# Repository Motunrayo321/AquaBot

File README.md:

# Rotatory-Distribution-System

combined_tests: tests the combined action of the different components. The fullTest() function tests the entire operation of the system.

unit_tests: used to test the operation of individual components

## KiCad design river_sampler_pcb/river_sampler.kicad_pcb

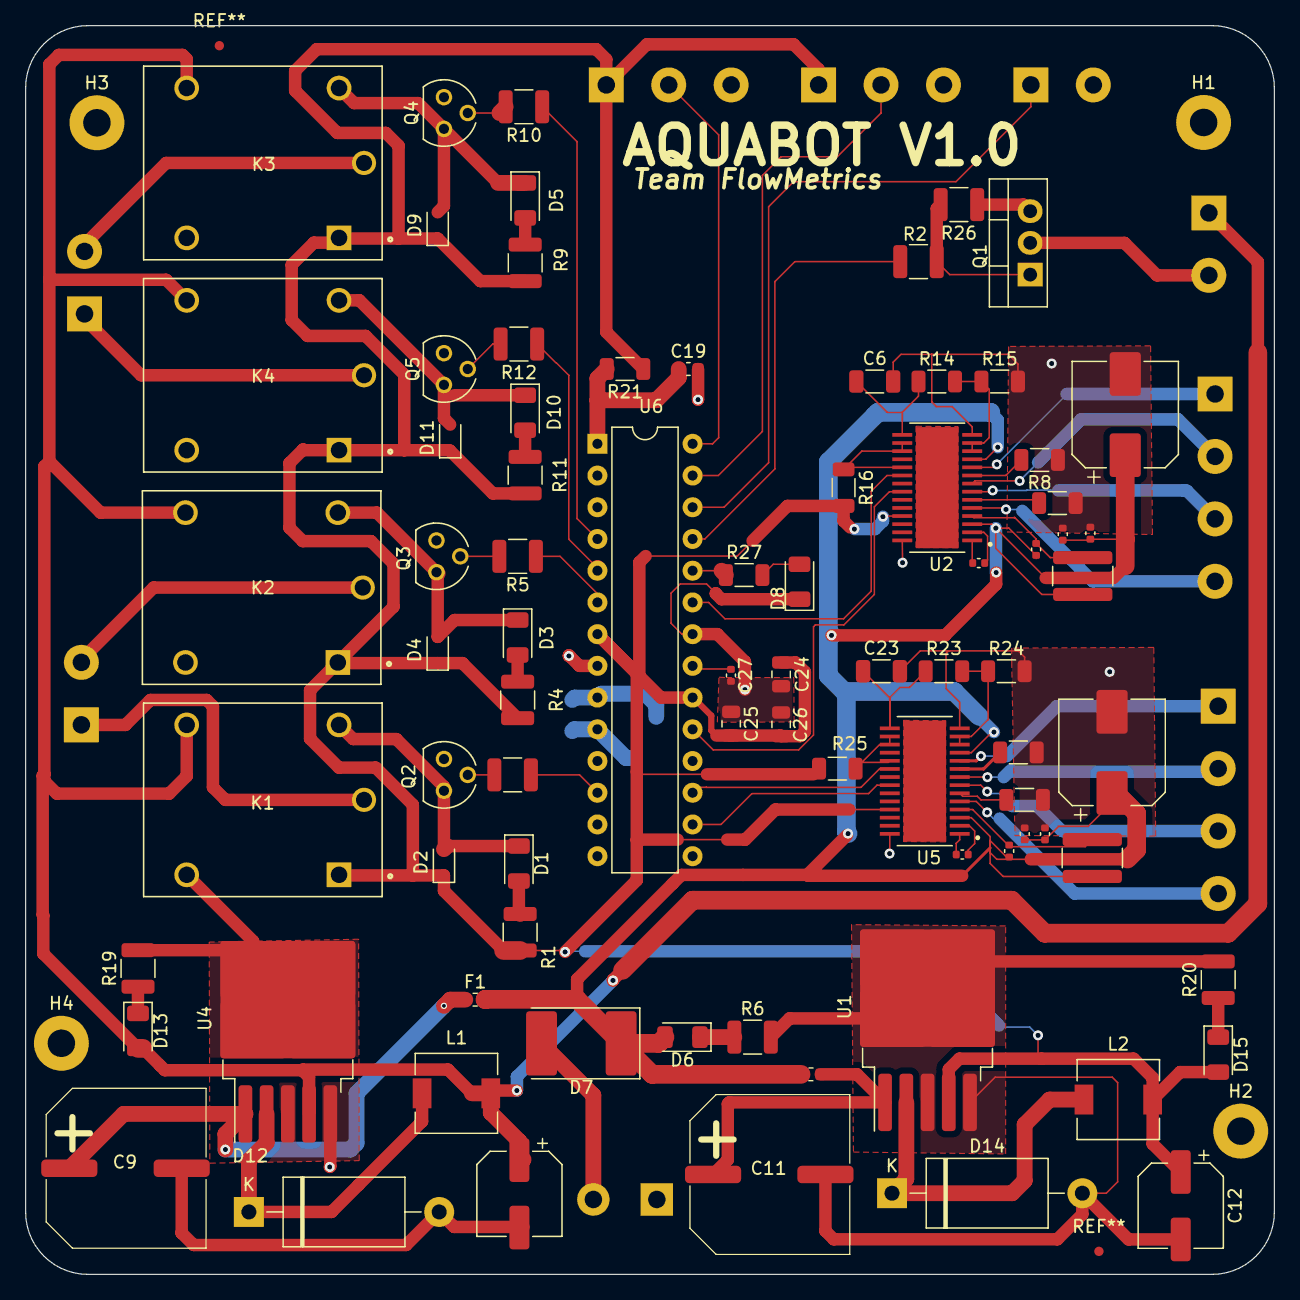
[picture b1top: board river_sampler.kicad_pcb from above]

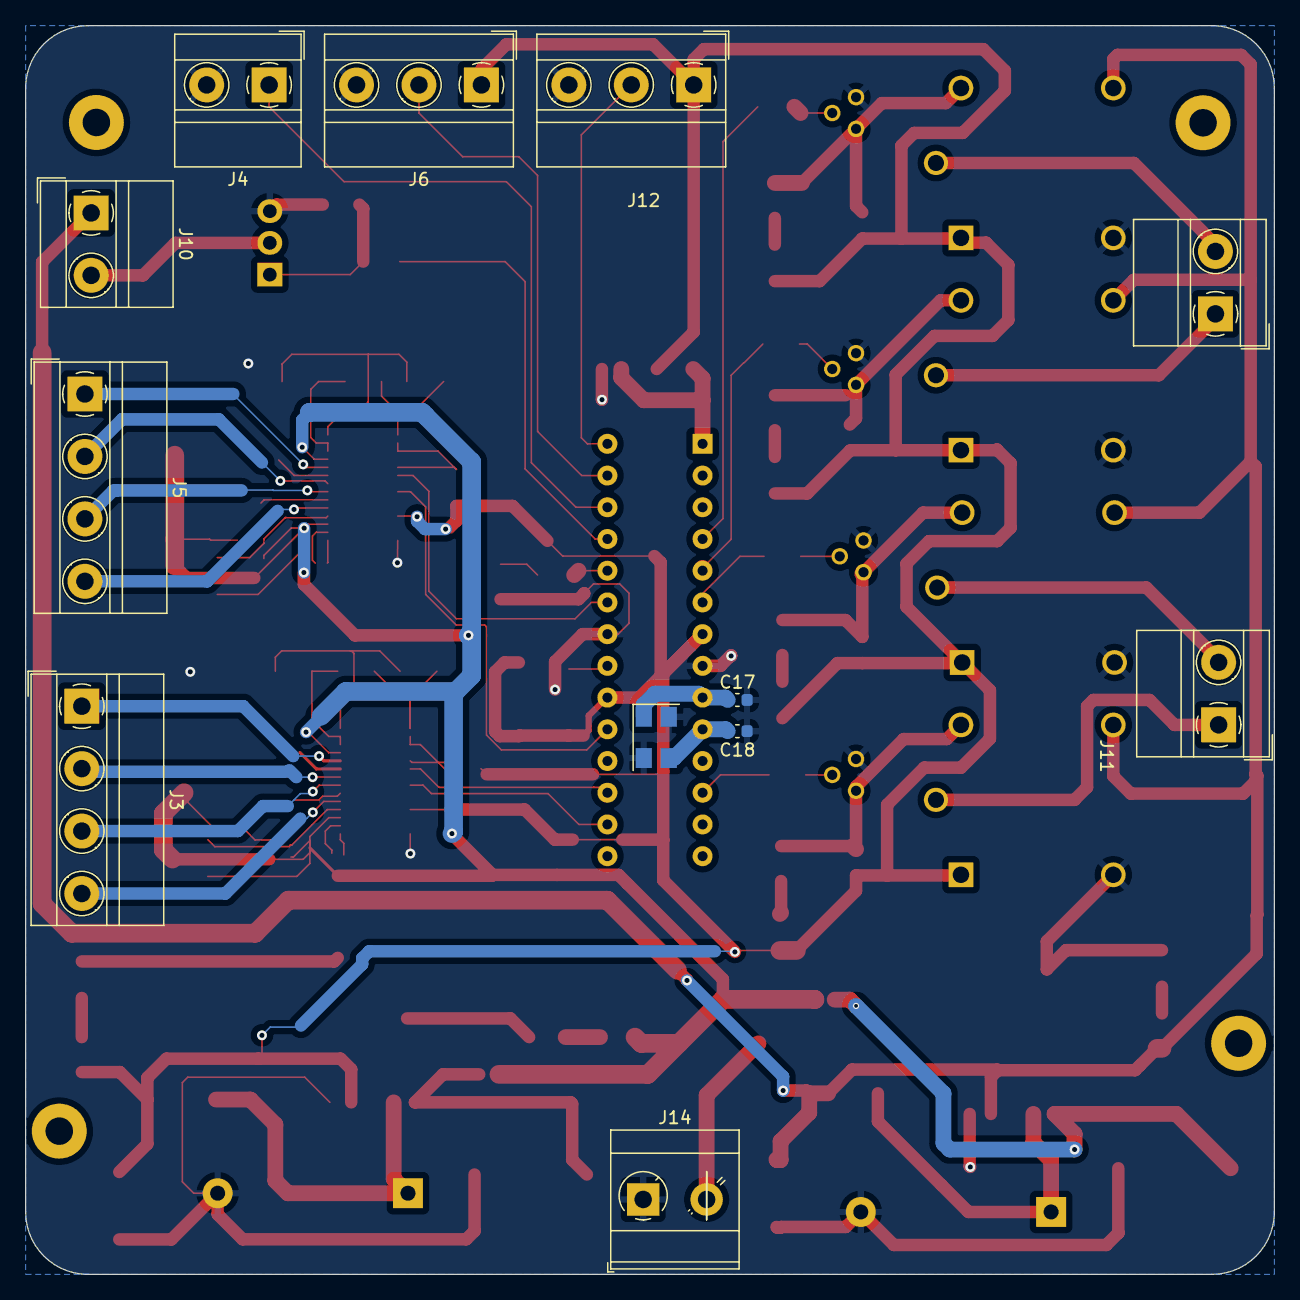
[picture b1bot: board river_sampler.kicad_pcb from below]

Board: 2 copper layers, 100.0 x 100.0 mm, 97 parts (12 on the bottom side), 72 nets.

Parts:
C1, C7: 100u; CP_Elec_8x10
C2, C3, C4, C5, C8, C20, C21, C22: 0.1u; C_0402_1005Metric
C6, C23: 0.47u; C_1206_3216Metric
C9, C11: 470u; C_SMD_470uF_12.5Dx13.5L
C10, C12: 220u; CP_Elec_6.3x7.7
C17, C18: 22p; C_0603_1608Metric
C19: 10u; C_0603_1608Metric
C24: 10u; C_0805_2012Metric
C25, C26: 0.1u; C_0805_2012Metric
C27: 100n; C_0402_1005Metric
D1, D3, D5, D6, D8, D10, D13, D15: LED; LED_1206_3216Metric
D2, D4, D9, D11: 1N4001; D_SOD-323
D7: D; D_3220_8050Metric
D12, D14: D_Schottky; D_DO-27_P15.24mm_Horizontal
F1, F2: 2A; Fuse_0603_1608Metric
H1, H2, H3, H4: MountingHole; MountingHole_2.2mm_M2_Pad
J3: rotary stepper; TerminalBlock_MetzConnect_Type011_RT05504HBWC_1x04_P5.00mm_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
J4: Limit Switch; TerminalBlock_MetzConnect_Type011_RT05502HBWC_1x02_P5.00mm_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
J5: Main pump; TerminalBlock_MetzConnect_Type011_RT05504HBWC_1x04_P5.00mm_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
J6: level sense; TerminalBlock_MetzConnect_Type011_RT05503HBWC_1x03_P5.00mm_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
J10: Flush Valve; TerminalBlock_MetzConnect_Type011_RT05502HBWC_1x02_P5.00mm_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
J11: minipump; TerminalBlock_MetzConnect_Type011_RT05502HBWC_1x02_P5.00mm_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
J12: Flow sense; TerminalBlock_MetzConnect_Type011_RT05503HBWC_1x03_P5.00mm_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
J13: lin act; TerminalBlock_MetzConnect_Type011_RT05502HBWC_1x02_P5.00mm_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
J14: 24V terminal; TerminalBlock_MetzConnect_Type073_RT02602HBLU_1x02_P5.08mm_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
K1, K2, K3, K4: Relay_SPDT; RELAY_SRD-05VDC-SL-C
L1, L2: L; L_6.3x6.3_H3
Q1: TIP120; TO-220-3_Vertical
Q2, Q3, Q4, Q5: NPN; TO92
R1, R2, R3, R4, R5, R6, R9, R10, R11, R12, R19, R20: 1k; R_1210_3225Metric
R7, R8, R17, R18: 200m; R_1206_3216Metric
R13, R22: 1M; R_1218_3246Metric
R14, R23: 7k; R_1206_3216Metric
R15, R24: 3k; R_1206_3216Metric
R16, R21, R25: 10k; R_1206_3216Metric
R26: 10k; R_1210_3225Metric
R27: 1k; R_1206_3216Metric
U1: LM2596S-5; TO-263-5_TabPin3
U2, U5: IC_TPS61196PWPRQ1
U4: LM2596S-12; TO-263-5_TabPin3
U6: ATmega328P-P; DIP-28_W7.62mm
Y1: 16M; Crystal_SMD_5032-4Pin_5.0x3.2mm

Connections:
+5V: C12.1, C24.1, C25.1, C26.1, D2.1 (K), D4.1 (K), D9.1 (K), D11.1 (K), D15.2 (A), J6.1, J12.1, K1.A1, K2.A1, K3.A1, K4.A1, L2.2, R1.2, R4.2, R9.2, R11.2, R16.2, R21.1, R25.2, U1.4 (FB), U2.25 (MODE1), U5.25 (MODE1), U6.7 (VCC), U6.20 (AVCC)
+12V: C10.1, D13.2 (A), J10.1, K1.14, K2.14, K3.14, K4.14, L1.2, U4.4 (FB)
+24V: C1.1, C2.1, C3.1, C4.1, C7.1, C8.1, C20.1, C21.1, D6.2 (A), D7.1 (K), F1.2, F2.2, R13.1, R22.1, U2.3 (VCP), U2.11 (VMB), U5.3 (VCP), U5.11 (VMB)
/ACT_1: R12.1, U6.5 (PD3)
/ACT_2: R10.1, U6.4 (PD2)
/Distribution System/5V relay1/RELAY_OUT: J11.2, K1.11
/Distribution System/5V relay2/RELAY_OUT: J13.1, K4.11
/Distribution System/5V relay3/RELAY_OUT: J13.2, K3.11
/Distribution System/5V relay/RELAY_OUT: J11.1, K2.11
/Distribution System/drv8825 driver1/3.3V_out: C6.1, R14.1, U2.15 (V3P3OUT)
/Distribution System/drv8825 driver1/MOT_1: J5.1, U2.5 (AOUT1)
/Distribution System/drv8825 driver1/MOT_2: J5.2, U2.7 (AOUT2)
/Distribution System/drv8825 driver1/MOT_3: J5.3, U2.8 (BOUT2)
/Distribution System/drv8825 driver1/MOT_4: J5.4, U2.10 (BOUT1)
/Distribution System/drv8825 driver1/RsenA: R7.2, U2.6 (ISENA)
/Distribution System/drv8825 driver1/RsenB: R8.2, U2.9 (ISENB)
/Distribution System/drv8825 driver/3.3V_out: C23.1, R23.1, U5.15 (V3P3OUT)
/Distribution System/drv8825 driver/MOT_1: J3.1, U5.5 (AOUT1)
/Distribution System/drv8825 driver/MOT_2: J3.2, U5.7 (AOUT2)
/Distribution System/drv8825 driver/MOT_3: J3.3, U5.8 (BOUT2)
/Distribution System/drv8825 driver/MOT_4: J3.4, U5.10 (BOUT1)
/Distribution System/drv8825 driver/RsenA: R17.2, U5.6 (ISENA)
/Distribution System/drv8825 driver/RsenB: R18.2, U5.9 (ISENB)
/FLOW_SENSE: J12.2, U6.28 (PC5)
/LEVELSENSE_FULL: J6.2, U6.27 (PC4)
/LIMIT_SW: J4.1, U6.26 (PC3)
/MAINPUMP_DIR: U2.20 (DIR), U6.23 (PC0)
/MAINPUMP_STEP: U2.22 (STEP), U6.19 (PB5)
/MOTOR_DIR: U5.20 (DIR), U6.17 (PB3)
/MOTOR_STEP: U5.22 (STEP), U6.16 (PB2)
/MP_1: R5.1, U6.6 (PD4)
/MP_2: R3.1, U6.12 (PD6)
/OSC1: C17.1, U6.9 (XTAL1/PB6), Y1.1
/OSC2: C18.1, U6.10 (XTAL2/PB7), Y1.3
/PULLUP: C19.1, R21.2, U6.1 (~RESET/PC6)
/VALVE_POWER: R2.1, U6.25 (PC2)
GND: C1.2, C2.2, C3.2, C6.2, C7.2, C8.2, C9.2, C10.2, C11.2, C12.2, C17.2, C18.2, C19.2, C20.2, C23.2, C24.2, C25.2, C26.2, C27.2, D8.1 (K), D12.2 (A), D14.2 (A), J4.2, J6.3, J12.3, J14.1, K1.12, K2.12, K3.12, K4.12, Q1.3 (E), Q2.3 (E), Q3.3 (E), Q4.3 (E), Q5.3 (E), R6.2, R7.1, R8.1, R15.2, R17.1, R18.1, R19.2, R20.2, R24.2, R26.1, U1.3 (GND), U1.5 (~ON/OFF), U2.14 (GND), U2.28 (GND), U4.3 (GND), U4.5 (~ON/OFF), U5.14 (GND), U5.28 (GND), U6.8 (GND), U6.22 (GND), Y1.2, Y1.4
unnamed: D1.2 (A), R1.1
unnamed: D1.1 (K), D2.2 (A), K1.A2, Q2.1 (C)
unnamed: D3.2 (A), R4.1
unnamed: D3.1 (K), D4.2 (A), K2.A2, Q3.1 (C)
unnamed: D5.2 (A), R9.1
unnamed: D5.1 (K), D9.2 (A), K3.A2, Q4.1 (C)
unnamed: D6.1 (K), R6.1
unnamed: D7.2 (A), J14.2
unnamed: D8.2 (A), R27.2
unnamed: D10.2 (A), R11.1
unnamed: D10.1 (K), D11.2 (A), K4.A2, Q5.1 (C)
unnamed: D12.1 (K), L1.1, U4.2 (OUT)
unnamed: D13.1 (K), R19.1
unnamed: D14.1 (K), L2.1, U1.2 (OUT)
unnamed: D15.1 (K), R20.1
unnamed: J10.2, Q1.2 (C)
unnamed: Q1.1 (B), R2.2, R26.2
unnamed: Q2.2 (B), R3.2
unnamed: Q3.2 (B), R5.2
unnamed: Q4.2 (B), R10.2
unnamed: Q5.2 (B), R12.2
unnamed: C11.1, F2.1, U1.1 (VIN)
unnamed: R14.2, R15.1, U2.12 (AVREF), U2.13 (BVREF)
unnamed: C5.1, U2.1 (CP1)
unnamed: C5.2, U2.2 (CP2)
unnamed: R16.1, U2.16 (nRESET), U2.17 (nSLEEP), U2.19 (DECAY)
unnamed: C4.2, R13.2, U2.4 (VMA)
unnamed: C9.1, F1.1, U4.1 (VIN)
unnamed: R23.2, R24.1, U5.12 (AVREF), U5.13 (BVREF)
unnamed: C22.1, U5.1 (CP1)
unnamed: C22.2, U5.2 (CP2)
unnamed: R25.1, U5.16 (nRESET), U5.17 (nSLEEP), U5.19 (DECAY)
unnamed: C21.2, R22.2, U5.4 (VMA)
unnamed: C27.1, U6.21 (AREF)
unnamed: R27.1, U6.24 (PC1)

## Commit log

2024-06-19 Added fv control code
2024-06-20 mini pump code
2024-06-20 Added sequence test for both motors, made the control code based on the flow (missing functions, to turn into modules)
2024-06-21 added header files
2024-06-21 moved old code to separate folder
2024-06-22 modified control code for servo mechanism
2024-06-23 unit tests for servo and stepper
2024-06-23 uses regular stepper library for simpler code
2024-06-24 started testing. Used normal stepper library
2024-06-24 minipump
2024-06-25 modified combined tests to include relay and linear actuator
2024-06-25 modified control interface code
2024-06-30 New motor driver
2024-07-01 flushing system
2024-07-03 microstepping
2024-07-03 code to flush the reservoir
2024-07-03 removed redundant file
2024-07-04 combined code for flushing and sampling
2024-07-10 modified control code
2024-07-10 organization
2024-07-10 Ready for integration!
    Tested flushing and filter back wash code with big pump.
2024-07-11 Included 2 funtions to activate low power mode
2024-07-11 Added 2 funtions to activate low power mode
2024-07-11 new flushing code with new pump
2024-08-08 pcb file
2024-08-29 cleaned up files
2024-08-29 added main schematic
2024-08-29 cleaned up unit tests
2024-08-29 pcb for high level prototype
2024-09-09 modifications to main
2025-03-25 Added Pictures of the machine
